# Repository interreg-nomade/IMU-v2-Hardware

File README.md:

# IMU-v2-Hardware

Design files can be found [here](/Design)

Manufacturing files can be found [here](/Gerber)

### Photos
Photos can be found [here](/Photos)

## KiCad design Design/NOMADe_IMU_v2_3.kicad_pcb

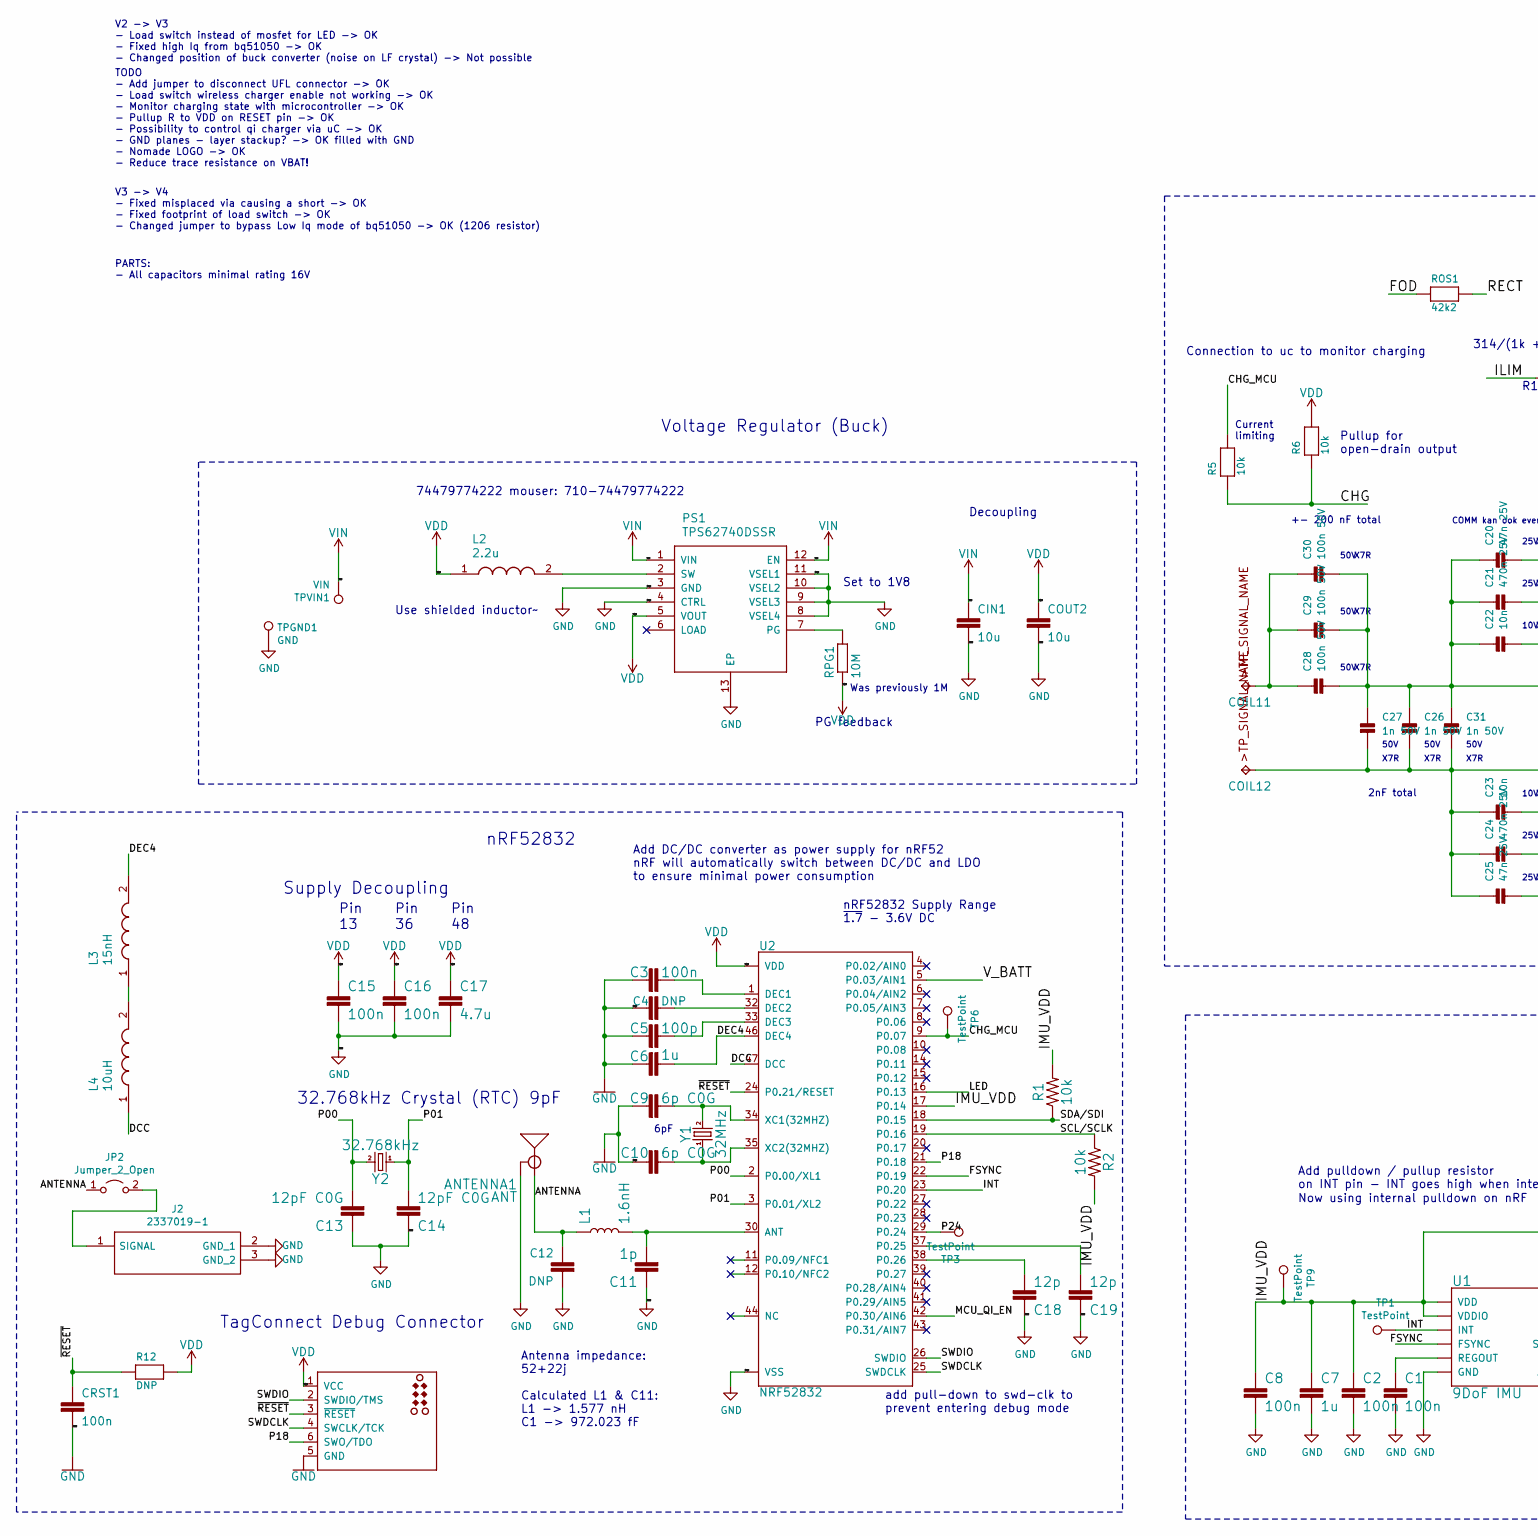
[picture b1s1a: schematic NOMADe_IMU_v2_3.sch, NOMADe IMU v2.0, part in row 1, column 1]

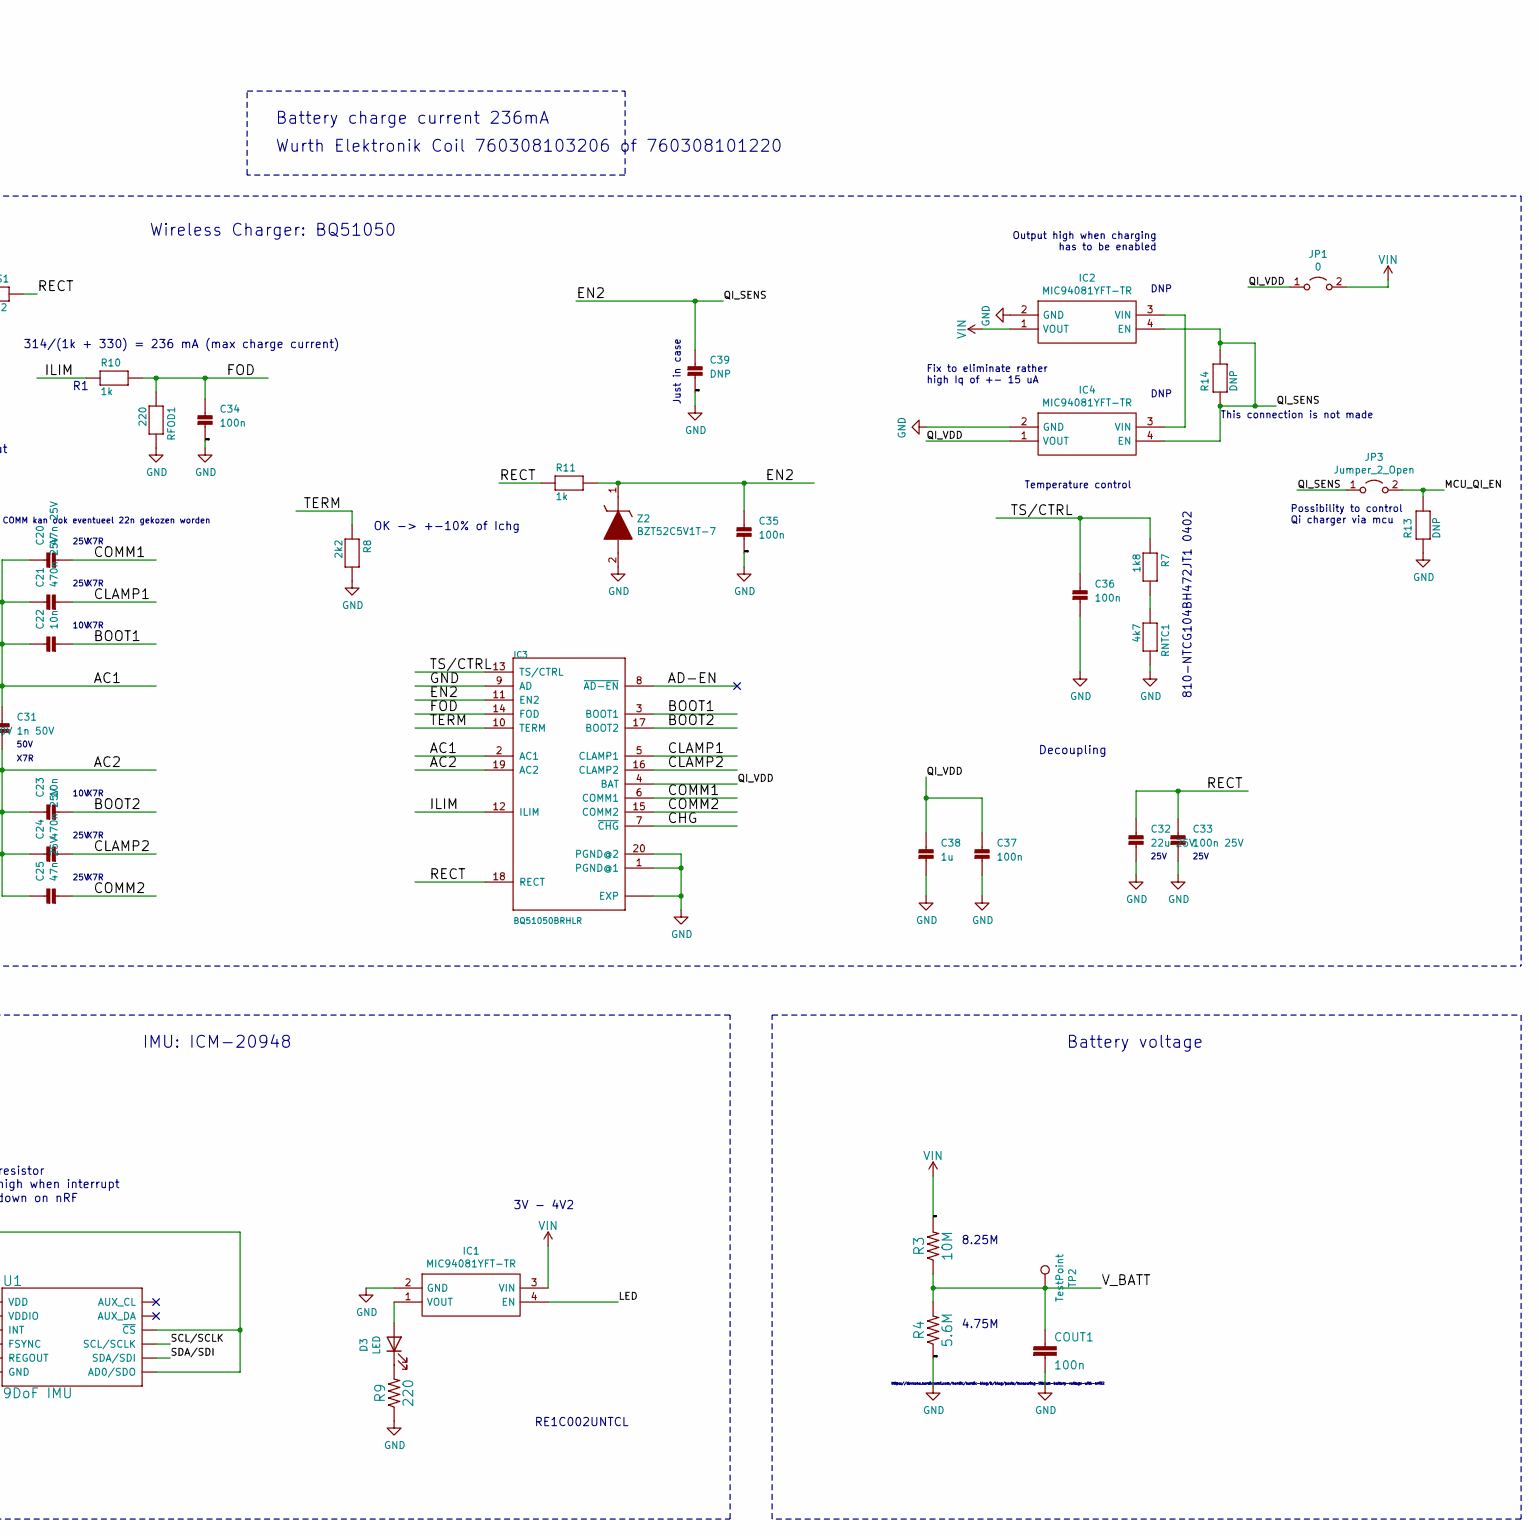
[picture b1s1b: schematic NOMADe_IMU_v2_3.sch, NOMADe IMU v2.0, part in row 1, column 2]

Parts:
ANTENNA1: ANT; TRACE_ANTENNA_2.4GHZ_15.2MM
C1, C2, C3, C8, C15, C16, C34, C35, C36, C37: 100n; C_0402_1005Metric
C4, C12, C39: DNP; C_0402_1005Metric
C5: 100p; C_0402_1005Metric
C6: 1u; C_0402_1005Metric
C7, C38: 1u; C_0603_1608Metric
C9, C10: 6p C0G; C_0402_1005Metric
C11: 1p; C_0402_1005Metric
C13, C14: 12pF C0G; C_0402_1005Metric
C17: 4.7u; C_0603_1608Metric
C18, C19: 12p; C_0402_1005Metric
C20, C25: 47n 25V; C_0603_1608Metric
C21, C24: 470n 25V; C_0603_1608Metric
C22, C23: 10n; C_0603_1608Metric
C26, C27, C31: 1n 50V; C_0603_1608Metric
C28, C29, C30: 100n 50V; C_0603_1608Metric
C32: 22u 25V; C_0805_2012Metric
C33: 100n 25V; C_0402_1005Metric
CIN1: 10u; C_0603_1608Metric
COIL11, COIL12: TPTP10SQ; TP10SQ
COUT1: 100n; C_0402_1005Metric
COUT2: 10u; C_0603_1608Metric
CRST1: 100n; C_0402_1005Metric
D3: LED; PinHeader_1x02_P1.27mm_Vertical
IC1, IC2, IC4: MIC94081YFT-TR; Mouser Part Number 998-MIC94081YFTTR
IC3: BQ51050BRHLR; QFN50P450X350X100-21N
J1: TC2030_SWD-MCP-NL; TC2030-MCP-NL
J2: 2337019-1; 23370191; Mouser Part Number 571-2337019-1
JP1: 0; R_1206_3216Metric
JP2: Jumper_2_Open; R_0402_1005Metric
JP3: Jumper_2_Open; SMT-JUMPER_2_NO_SILK
L1: 1.6nH; 0402
L2: 2.2u; INDC2012X145N
L3: 15nH; L_0402_1005Metric
L4: 10uH; L_0603_1608Metric
PS1: TPS62740DSSR; SON50P200X300X80-13N
R1, R2, R5, R6: 10k; C_0402_1005Metric
R3: 10M; R_0603_1608Metric
R4: 5.6M; R_0603_1608Metric
R7: 1k8; R_0402_1005Metric
R8: 2k2; R_0603_1608Metric
R9: 220; R_0402_1005Metric
R10, R11: 1k; R_0603_1608Metric
R12, R13: DNP; C_0402_1005Metric
R14: DNP; R_0603_1608Metric
RFOD1: 220; R_0603_1608Metric
RNTC1: 4k7; R_0402_1005Metric
ROS1: 42k2; R_0603_1608Metric
RPG1: 10M; R_0603_1608Metric
TP1, TP2, TP3, TP6, TP9: TestPoint; TestPoint_Pad_D1.0mm
TPGND1: GND; TestPoint_Pad_2.0x2.0mm
TPVIN1: VIN; TestPoint_Pad_2.0x2.0mm
U1: 9DoF IMU; QFN24-3X3
U2: NRF52832; QFN48-6X6MM
Y1: 32MHz; CRYSTAL-SMD-2.0X1.6MM
Y2: 32.768kHz; CRYSTAL-SMD-3.2X1.5MM
Z2: BZT52C5V1T-7; SODFL1608X65N; Mouser Part Number 621-BZT52C5V1T-7

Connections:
/AC1: C20.1, C21.1, C22.1, C26.1, C27.1, C28.2, C29.2, C30.2, C31.1, IC3.2 (AC1)
/AC2: C23.1, C24.1, C25.1, C26.2, C27.2, C31.2, COIL12.TP, IC3.19 (AC2)
/AD-EN: IC3.8 (~AD-EN)
/ANTENNA: ANTENNA1.ANT (SIGNAL), C12.1, JP2.1 (A), L1.1
/BOOT1: C22.2, IC3.3 (BOOT1)
/BOOT2: C23.2, IC3.17 (BOOT2)
/CHG: IC3.7 (~CHG), R5.1, R6.1
/CHG_MCU: R5.2, TP6.1, U2.9 (P0.07)
/CLAMP1: C21.2, IC3.5 (CLAMP1)
/CLAMP2: C24.2, IC3.16 (CLAMP2)
/COMM1: C20.2, IC3.6 (COMM1)
/COMM2: C25.2, IC3.15 (COMM2)
/DCC: L4.1, U2.47 (DCC)
/DEC4: C6.2, L3.2, U2.46 (DEC4)
/EN2: C35.1, C39.1, IC2.4 (EN), IC3.11 (EN2), IC4.4 (EN), JP3.1 (A), R11.2, R14.1, R14.2, Z2.1
/FOD: C34.1, IC3.14 (FOD), R10.2, RFOD1.1, ROS1.1
/FSYNC: U1.11 (FSYNC), U2.22 (P0.19)
/ILIM: IC3.12 (ILIM), R10.1
/IMU_VDD: C2.1, C7.1, C8.1, R1.2, R2.2, TP9.1, U1.8 (VDDIO), U1.9 (AD0/SDO), U1.13 (VDD), U1.22 (~CS), U2.17 (P0.14)
/INT: TP1.1, U1.12 (INT), U2.23 (P0.20)
/LED: IC1.4 (EN), U2.16 (P0.13)
/MCU_QI_EN: JP3.2 (B), R13.2, U2.42 (P0.30/AIN6)
/P00: C13.2, U2.2 (P0.00/XL1), Y2.P$2 (2)
/P01: C14.2, U2.3 (P0.01/XL2), Y2.P$1 (1)
/P18: J1.6 (SWO/TDO), U2.21 (P0.18)
/P24: TP3.1, U2.29 (P0.24)
/QI_VDD: C37.1, C38.1, IC3.4 (BAT), IC4.1 (VOUT), JP1.1 (A)
/RECT: C32.1, C33.1, IC3.18 (RECT), R11.1, ROS1.2
/SCL/SCLK: R2.1, U1.23 (SCL/SCLK), U2.19 (P0.16)
/SDA/SDI: R1.1, U1.24 (SDA/SDI), U2.18 (P0.15)
/SWDCLK: J1.4 (SWCLK/TCK), U2.25 (SWDCLK)
/SWDIO: J1.2 (SWDIO/TMS), U2.26 (SWDIO)
/TERM: IC3.10 (TERM), R8.1
/TS/CTRL: C36.1, IC3.13 (TS/CTRL), R7.1
/V_BATT: COUT1.1, R3.1, R4.2, TP2.1, U2.5 (P0.03/AIN1)
/~RESET~: CRST1.1, J1.3 (~RESET), R12.1, U2.24 (P0.21/RESET)
GND: ANTENNA1.GND, C1.2, C2.2, C3.1, C4.1, C5.1, C6.1, C7.2, C8.2, C9.1, C10.2, C11.1, C12.2, C13.1, C14.1, C15.2, C16.2, C17.2, C18.1, C19.1, C32.2, C33.2, C34.2, C35.2, C36.2, C37.2, C38.2, C39.2, CIN1.2, COUT1.2, COUT2.2, CRST1.2, IC1.2 (GND), IC2.2 (GND), IC3.1 (PGND@1), IC3.9 (AD), IC3.20 (PGND@2), IC3.21 (EXP), IC3.22 (EXP), IC3.23 (EXP), IC3.24 (EXP), IC3.25 (EXP), IC3.26 (EXP), IC3.27 (EXP), IC3.28 (EXP), IC3.29 (EXP), IC3.30 (EXP), IC3.31 (EXP), IC3.32 (EXP), IC3.33 (EXP), IC4.2 (GND), J1.5 (GND), J2.2 (GND_1), J2.3 (GND_2), PS1.3 (GND), PS1.4 (CTRL), PS1.8 (VSEL4), PS1.9 (VSEL3), PS1.10 (VSEL2), PS1.11 (VSEL1), PS1.13 (EP), R4.1, R8.2, R9.1, R13.1, RFOD1.2, RNTC1.2, TPGND1.1, U1.18 (GND), U1.20 (GND), U2.31 (VSS), U2.45 (VSS), U2.EP (VSS), Z2.2
unnamed: C1.1, U1.10 (REGOUT)
unnamed: C3.2, U2.1 (DEC1)
unnamed: C4.2, U2.32 (DEC2)
unnamed: C5.2, U2.33 (DEC3)
unnamed: C9.2, U2.34 (XC1(32MHZ)), Y1.3 (2)
unnamed: C10.1, U2.35 (XC2(32MHZ)), Y1.1
unnamed: C11.2, L1.2, U2.30 (ANT)
unnamed: C18.2, U2.38 (P0.26)
unnamed: C19.2, U2.37 (P0.25)
unnamed: C28.1, C29.1, C30.1, COIL11.TP
unnamed: D3.1 (K), R9.2
unnamed: D3.2 (A), IC1.1 (VOUT)
unnamed: IC2.3 (VIN), IC4.3 (VIN)
unnamed: J2.1 (SIGNAL), JP2.2 (B)
unnamed: L2.2, PS1.2 (SW)
unnamed: L3.1, L4.2
unnamed: PS1.7 (PG), RPG1.2
unnamed: R7.2, RNTC1.1
VDD: C15.1, C16.1, C17.1, COUT2.1, J1.1 (VCC), L2.1, PS1.5 (VOUT), R6.2, R12.2, RPG1.1, U2.13 (VDD), U2.36 (VDD), U2.48 (VDD)
VIN: CIN1.1, IC1.3 (VIN), IC2.1 (VOUT), JP1.2 (B), PS1.1 (VIN), PS1.12 (EN), R3.2, TPVIN1.1

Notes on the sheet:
nRF52832
TagConnect Debug Connector
nRF52832 Supply Range ~1.7 - 3.6V DC~
74479774222 mouser: 710-74479774222
Decoupling
Set to 1V8
PG feedback
Voltage Regulator (Buck)
IMU: ICM-20948
3V - 4V2
RE1C002UNTCL
Add pulldown / pullup resistor on INT pin - INT goes high when interrupt
Add DC/DC converter as power supply for nRF52 nRF will automatically switch between DC/DC and LDO to ensure minimal power consumption
Use shielded inductor~~
add pull-down to swd-clk to prevent entering debug mode
4.75M
8.25M
https://devzone.nordicsemi.com/nordic/nordic-blog/b/blog/posts/measuring-lithium-battery-voltage-with-nrf52
Now using internal pulldown on nRF
Antenna impedance: 52+22j Calculated L1 & C11: L1 -> 1.577 nH C1 -> 972.023 fF
10V
25V
COMM kan ook eventueel 22n gekozen worden
50V
X7R
314/(1k + 330) = 236 mA (max charge current)
Wurth Elektronik Coil 760308103206 of 760308101220
Battery charge current 236mA
Wireless Charger: BQ51050
Connection to uc to monitor charging
OK -> +-10% of Ichg
810-NTCG104BH472JT1 0402
Output high when charging has to be enabled
2nF total
+- 200 nF total
TODO - Add jumper to disconnect UFL connector -> OK - Load switch wireless charger enable not working -> OK - Monitor charging state with microcontroller -> OK - Pullup R to VDD on RESET pin -> OK - Possibility to control qi charger via uC -> OK - GND planes - layer stackup? -> OK filled with GND -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
32.768kHz Crystal (RTC) 9pF
Supply Decoupling
Pin 48
Pin 36

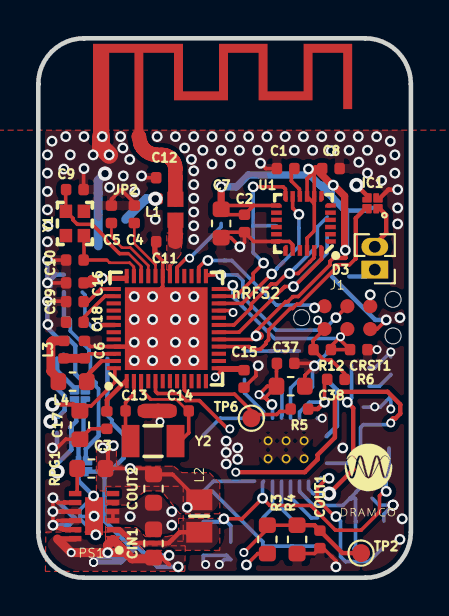
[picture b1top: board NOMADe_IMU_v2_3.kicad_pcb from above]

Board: 4 copper layers, 20.7 x 30.0 mm, 91 parts (0 on the bottom side), 56 nets.

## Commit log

2022-03-03 Design files PCB
2022-03-03 3D prints case
2022-03-07 Photos

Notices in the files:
parts and their libraries:
Copyright 2021 Accelerated Designs. All rights reserved.
©2009 ROFA.cz - modified and updated by Robert Darlington ‹rdarlington@gmail.com›
